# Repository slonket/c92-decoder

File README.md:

# c92-decoder

### An MM1/MM2/Lenz decoder for classic Märklin locomotives and the pre-mfx digital systems.

The c92 decoder was spawned out of a passion for the classic (pre-mfx) Märklin digital systems. The controllers of this era operated with three different protocols:
- MM1 (6020, 6021, 6022, 6023)
- MM2 (6021)
- Lenz (6027, 6029)

However, no single decoder from this era can operate on all three protocols, nor with all of their capabilities. Furthermore, there is a matrix of incompatibility between different controllers and combinations of decoders using MM1 and MM2. The c92 decoder is a superset of all decoder capabilities and their respective protocols; a universal classic decoder.

### Cloning

This project uses [`slonket-footprints`](https://github.com/slonket/slonket-footprints) as a submodule for all PCB designs. All KiCAD projects within this repository are configured to use the submodule libraries with local paths. Run the following to clone the repository with its submodule:
```
git clone --recurse-submodules https://github.com/slonket/c92-decoder.git
```

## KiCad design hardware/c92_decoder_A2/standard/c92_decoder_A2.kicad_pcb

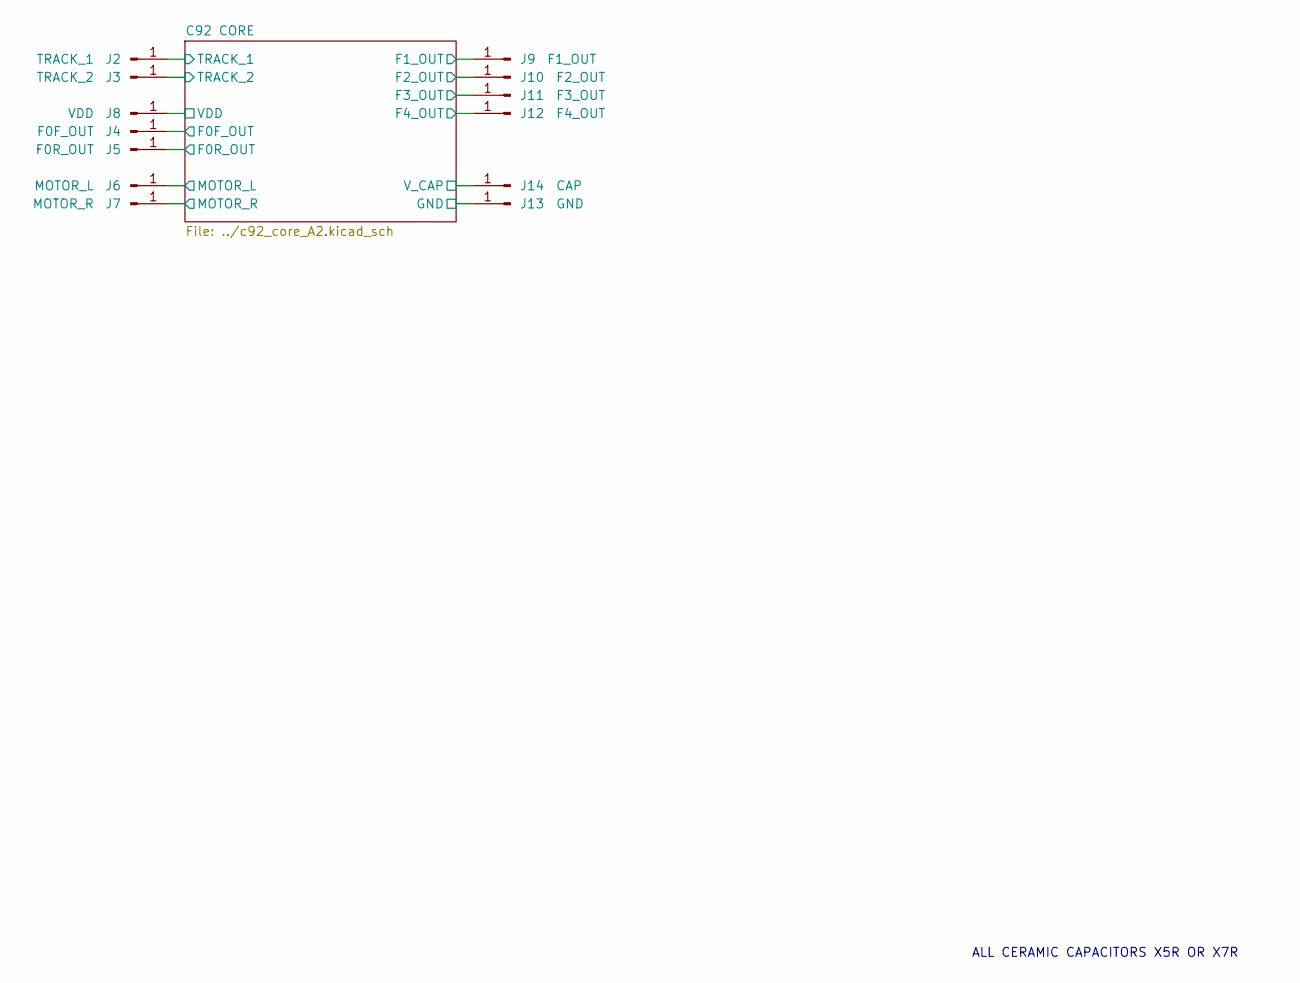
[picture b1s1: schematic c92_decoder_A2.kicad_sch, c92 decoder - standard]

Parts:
J2: TRACK_1; J_Pad_1mm_2mm
J3: TRACK_2; J_Pad_1mm_2mm
J4: F0F_OUT; J_Pad_1mm_2mm
J5: F0R_OUT; J_Pad_1mm_2mm
J6: MOTOR_L; J_Pad_1mm_2mm
J7: MOTOR_R; J_Pad_1mm_2mm
J8: VDD; J_Pad_1mm_2mm
J9: F1_OUT; J_Pad_1mm_2mm
J10: F2_OUT; J_Pad_1mm_2mm
J11: F3_OUT; J_Pad_1mm_2mm
J12: F4_OUT; J_Pad_1mm_2mm
J13: GND; J_Pad_1mm_2mm
J14: CAP; J_Pad_1mm_2mm

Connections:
/C92 CORE/F0F_OUT: J4.1 (Pin_1_1); also elsewhere on the board
/C92 CORE/F0R_OUT: J5.1 (Pin_1_1); also elsewhere on the board
/C92 CORE/F1_OUT: J9.1 (Pin_1_1); also elsewhere on the board
/C92 CORE/F2_OUT: J10.1 (Pin_1_1); also elsewhere on the board
/C92 CORE/F3_OUT: J11.1 (Pin_1_1); also elsewhere on the board
/C92 CORE/F4_OUT: J12.1 (Pin_1_1); also elsewhere on the board
/C92 CORE/MOTOR_L: J6.1 (Pin_1_1); also elsewhere on the board
/C92 CORE/MOTOR_R: J7.1 (Pin_1_1); also elsewhere on the board
/C92 CORE/TRACK_1: J2.1 (Pin_1_1); also elsewhere on the board
/C92 CORE/TRACK_2: J3.1 (Pin_1_1); also elsewhere on the board
/C92 CORE/V_CAP: J14.1 (Pin_1_1); also elsewhere on the board
GND: J13.1 (Pin_1_1); also elsewhere on the board
VDD: J8.1 (Pin_1_1); also elsewhere on the board

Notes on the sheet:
ALL CERAMIC CAPACITORS X5R OR X7R

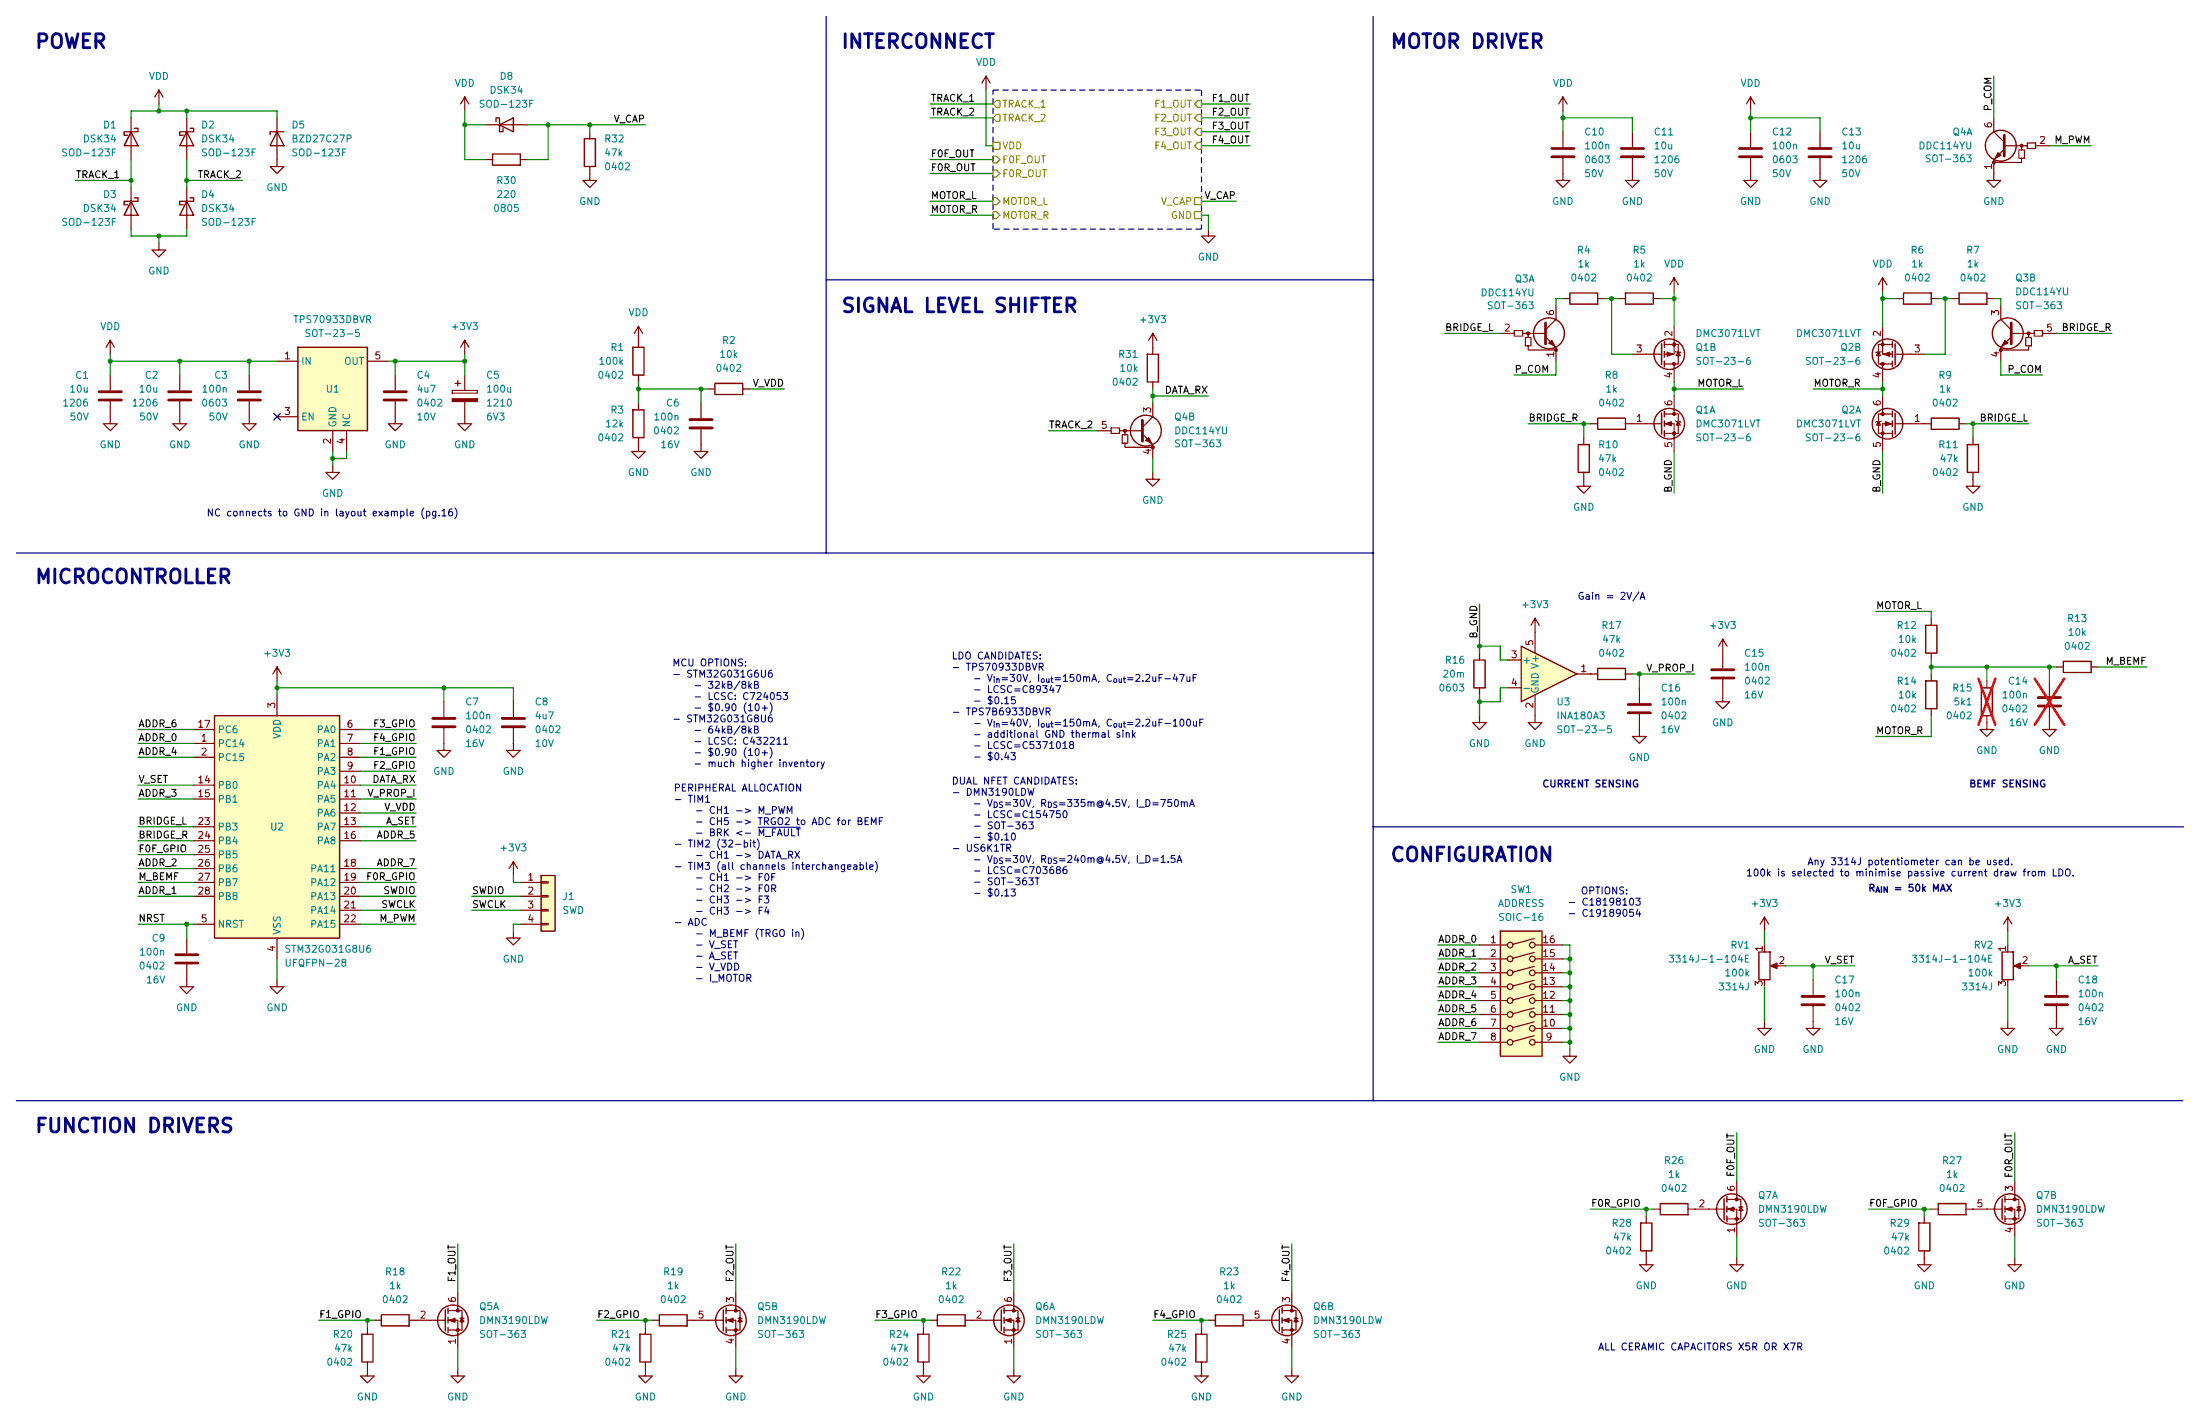
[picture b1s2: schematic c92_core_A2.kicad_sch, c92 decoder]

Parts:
C1, C2, C11, C13: 10u; C_1206; Voltage 50V; LCSC C13585
C3, C10, C12: 100n; C_0603; Voltage 50V; LCSC C14663
C4, C8: 4u7; C_0402; Voltage 10V; LCSC C23733
C5: 100u; CP_1210_CASE_B; Voltage 6V3; LCSC C16133
C6, C7, C9, C15, C16, C17, C18: 100n; C_0402; Voltage 16V; LCSC C1525
C14: 100n; C_0402; Voltage 16V; LCSC C1525; not fitted
D1, D2, D3, D4, D8: DSK34; D_SOD-123F; LCSC C7502709
D5: BZD27C27P; D_SOD-123F; LCSC C5455754
J1: SWD; J_Pad_4_1.5mm
Q1, Q2: DMC3071LVT; U_SOT-23-6; LCSC C17543297
Q3, Q4: DDC114YU; U_SOT-363; LCSC C151389
Q5, Q6, Q7: DMN3190LDW; U_SOT-363; LCSC C154750
R1: 100k; R_0402; LCSC C25741
R2, R12, R13, R14, R31: 10k; R_0402; LCSC C25744
R3: 12k; R_0402; LCSC C25752
R4, R5, R6, R7, R8, R9, R18, R19, R22, R23, R26, R27: 1k; R_0402; LCSC C11702
R10, R11, R17, R20, R21, R24, R25, R28, R29, R32: 47k; R_0402; LCSC C25792
R15: 5k1; R_0402; LCSC C25905; not fitted
R16: 20m; R_0603; LCSC C156372
R30: 220; R_0805; LCSC C17557
RV1, RV2: 3314J-1-104E; RV_BOURNS_3314J; LCSC C51284
SW1: ADDRESS; SW_DIP_8_P1.27; LCSC C18198103
U1: TPS70933DBVR; U_SOT-23-5; LCSC C89347
U2: STM32G031G8U6; U_STM_UFQFPN-28_4x4_P0.5; LCSC C432211
U3: INA180A3; U_SOT-23-5; LCSC C122882

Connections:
+3V3: C4.1, C5.1, C7.1, C8.1, C15.1, J1.1, R31.2, RV1.1, RV2.1, U1.5 (OUT), U2.3 (VDD), U3.5 (V+)
/C92 CORE/ADDR_0: SW1.1, U2.1 (PC14)
/C92 CORE/ADDR_1: SW1.2, U2.28 (PB8)
/C92 CORE/ADDR_2: SW1.3, U2.26 (PB6)
/C92 CORE/ADDR_3: SW1.4, U2.15 (PB1)
/C92 CORE/ADDR_4: SW1.5, U2.2 (PC15)
/C92 CORE/ADDR_5: SW1.6, U2.16 (PA8)
/C92 CORE/ADDR_6: SW1.7, U2.17 (PC6)
/C92 CORE/ADDR_7: SW1.8, U2.18 (PA11)
/C92 CORE/A_SET: C18.1, RV2.2, U2.13 (PA7)
/C92 CORE/BRIDGE_L: Q3.2 (B1), R9.1, R11.2, U2.23 (PB3)
/C92 CORE/BRIDGE_R: Q3.5 (B2), R8.1, R10.2, U2.24 (PB4)
/C92 CORE/B_GND: Q1.5 (S), Q2.5 (S), R16.1, U3.3 (+)
/C92 CORE/DATA_RX: Q4.3 (C2), R31.1, U2.10 (PA4)
/C92 CORE/F0F_GPIO: R27.1, R29.2, U2.25 (PB5)
/C92 CORE/F0F_OUT: Q7.6 (D); also elsewhere on the board
/C92 CORE/F0R_GPIO: R26.1, R28.2, U2.19 (PA12)
/C92 CORE/F0R_OUT: Q7.3 (D); also elsewhere on the board
/C92 CORE/F1_GPIO: R18.1, R20.2, U2.8 (PA2)
/C92 CORE/F1_OUT: Q5.6 (D); also elsewhere on the board
/C92 CORE/F2_GPIO: R19.1, R21.2, U2.9 (PA3)
/C92 CORE/F2_OUT: Q5.3 (D); also elsewhere on the board
/C92 CORE/F3_GPIO: R22.1, R24.2, U2.6 (PA0)
/C92 CORE/F3_OUT: Q6.6 (D); also elsewhere on the board
/C92 CORE/F4_GPIO: R23.1, R25.2, U2.7 (PA1)
/C92 CORE/F4_OUT: Q6.3 (D); also elsewhere on the board
/C92 CORE/MOTOR_L: Q1.4 (D), Q1.6 (D), R12.2; also elsewhere on the board
/C92 CORE/MOTOR_R: Q2.4 (D), Q2.6 (D), R14.1; also elsewhere on the board
/C92 CORE/M_BEMF: R13.2, U2.27 (PB7)
/C92 CORE/M_PWM: Q4.2 (B1), U2.22 (PA15)
/C92 CORE/NRST: C9.1, U2.5 (NRST)
/C92 CORE/P_COM: Q3.1 (E1), Q3.4 (E2), Q4.6 (C1)
/C92 CORE/SWCLK: J1.3, U2.21 (PA14)
/C92 CORE/SWDIO: J1.2, U2.20 (PA13)
/C92 CORE/TRACK_1: D1.2 (A), D3.1 (K); also elsewhere on the board
/C92 CORE/TRACK_2: D2.2 (A), D4.1 (K), Q4.5 (B2); also elsewhere on the board
/C92 CORE/V_CAP: D8.2 (A), R30.2, R32.2; also elsewhere on the board
/C92 CORE/V_PROP_I: C16.1, R17.2, U2.11 (PA5)
/C92 CORE/V_SET: C17.1, RV1.2, U2.14 (PB0)
/C92 CORE/V_VDD: R2.2, U2.12 (PA6)
GND: C1.2, C2.2, C3.2, C4.2, C5.2, C6.2, C7.2, C8.2, C9.2, C10.2, C11.2, C12.2, C13.2, C14.2, C15.2, C16.2, C17.2, C18.2, D3.2 (A), D4.2 (A), D5.2 (A), J1.4, Q4.1 (E1), Q4.4 (E2), Q5.1 (S), Q5.4 (S), Q6.1 (S), Q6.4 (S), Q7.1 (S), Q7.4 (S), R3.1, R10.1, R11.1, R15.1, R16.2, R20.1, R21.1, R24.1, R25.1, R28.1, R29.1, R32.1, RV1.3, RV2.3, SW1.9, SW1.10, SW1.11, SW1.12, SW1.13, SW1.14, SW1.15, SW1.16, U1.2 (GND), U1.4 (NC), U2.4 (VSS), U3.2 (GND), U3.4 (-); also elsewhere on the board
unnamed: C6.1, R1.1, R2.1, R3.2
unnamed: C14.1, R12.1, R13.1, R14.2, R15.2
unnamed: Q1.1 (G), R8.2
unnamed: Q1.3 (G), R4.2, R5.2
unnamed: Q2.1 (G), R9.2
unnamed: Q2.3 (G), R6.2, R7.1
unnamed: Q3.6 (C1), R4.1
unnamed: Q3.3 (C2), R7.2
unnamed: Q5.2 (G), R18.2
unnamed: Q5.5 (G), R19.2
unnamed: Q6.2 (G), R22.2
unnamed: Q6.5 (G), R23.2
unnamed: Q7.2 (G), R26.2
unnamed: Q7.5 (G), R27.2
unnamed: R17.1, U3.1
VDD: C1.1, C2.1, C3.1, C10.1, C11.1, C12.1, C13.1, D1.1 (K), D2.1 (K), D5.1 (K), D8.1 (K), Q1.2 (S), Q2.2 (S), R1.2, R5.1, R6.1, R30.1, U1.1 (IN); also elsewhere on the board

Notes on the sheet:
PERIPHERAL ALLOCATION - TIM1 - CH1 -> M_PWM - CH5 -> TRGO2 to ADC for BEMF - BRK <- ~{M_FAULT} - TIM2 (32-bit) - CH1 -> DATA_RX - TIM3 (all channels interchangeable) - CH1 -> F0F - CH2 -> F0R - CH3 -> F3 - CH3 -> F4 - ADC - M_BEMF (TRGO in) - V_SET - A_SET - V_VDD - I_MOTOR
Any 3314J potentiometer can be used. 100k is selected to minimise passive current draw from LDO.
MOTOR DRIVER
ALL CERAMIC CAPACITORS X5R OR X7R
SIGNAL LEVEL SHIFTER
POWER
Gain = 2V/A
DUAL NFET CANDIDATES: - DMN3190LDW - V_{DS}=30V, R_{DS}=335m@4.5V, I_D=750mA - LCSC=C154750 - SOT-363 - $0.10 - US6K1TR - V_{DS}=30V, R_{DS}=240m@4.5V, I_D=1.5A - LCSC=C703686 - SOT-363T - $0.13
OPTIONS: - C18198103 - C19189054
CURRENT SENSING
NC connects to GND in layout example (pg.16)
BEMF SENSING
MCU OPTIONS: - STM32G031G6U6 - 32kB/8kB - LCSC: C724053 - $0.90 (10+) - STM32G031G8U6 - 64kB/8kB - LCSC: C432211 - $0.90 (10+) - much higher inventory
INTERCONNECT
CONFIGURATION
FUNCTION DRIVERS
MICROCONTROLLER
LDO CANDIDATES: - TPS70933DBVR - V_{in}=30V, I_{out}=150mA, C_{out}=2.2uF-47uF - LCSC=C89347 - $0.15 - TPS7B6933DBVR - V_{in}=40V, I_{out}=150mA, C_{out}=2.2uF-100uF - additional GND thermal sink - LCSC=C5371018 - $0.43
R_{AIN} = 50k MAX

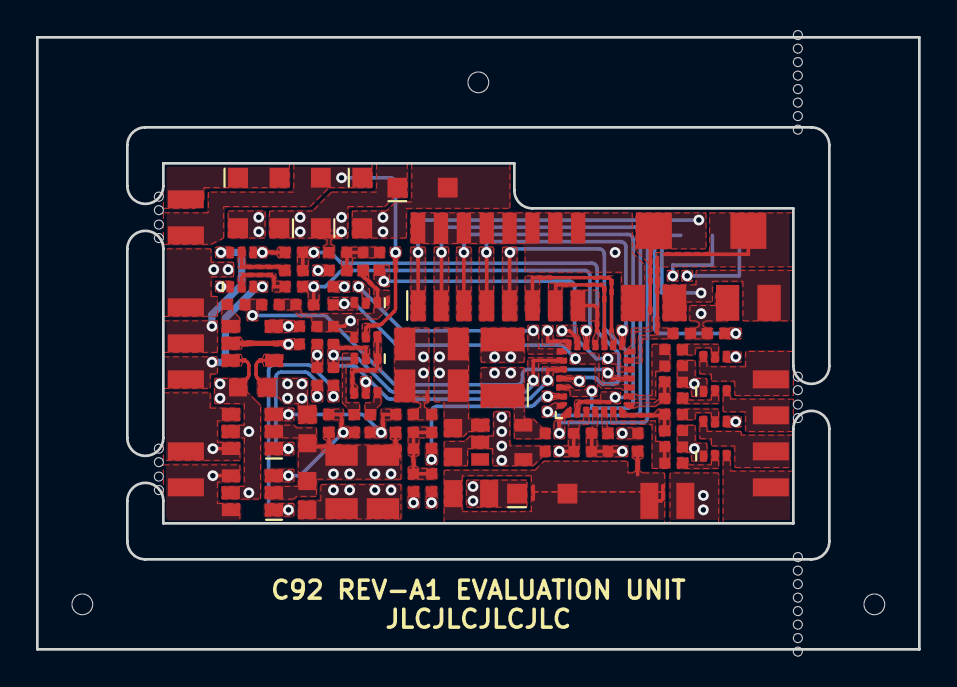
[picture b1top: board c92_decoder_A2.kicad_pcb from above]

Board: 4 copper layers, 49.0 x 34.0 mm, 83 parts (1 on the bottom side), 57 nets.

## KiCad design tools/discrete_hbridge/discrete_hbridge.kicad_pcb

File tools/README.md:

# c92-decoder - tools

### discrete_hbridge

A development board for the discrete H-bridge design used in the c92 decoder. The H-bridge is unique in being able to operate with low-side FETs always on, while PWM is applied only to the top FETs. This mode is necessary for BEMF measurement referenced to decoder ground.

### hubert_mounts

Mounting hardware for a breadboard to be fastened atop Hubert.

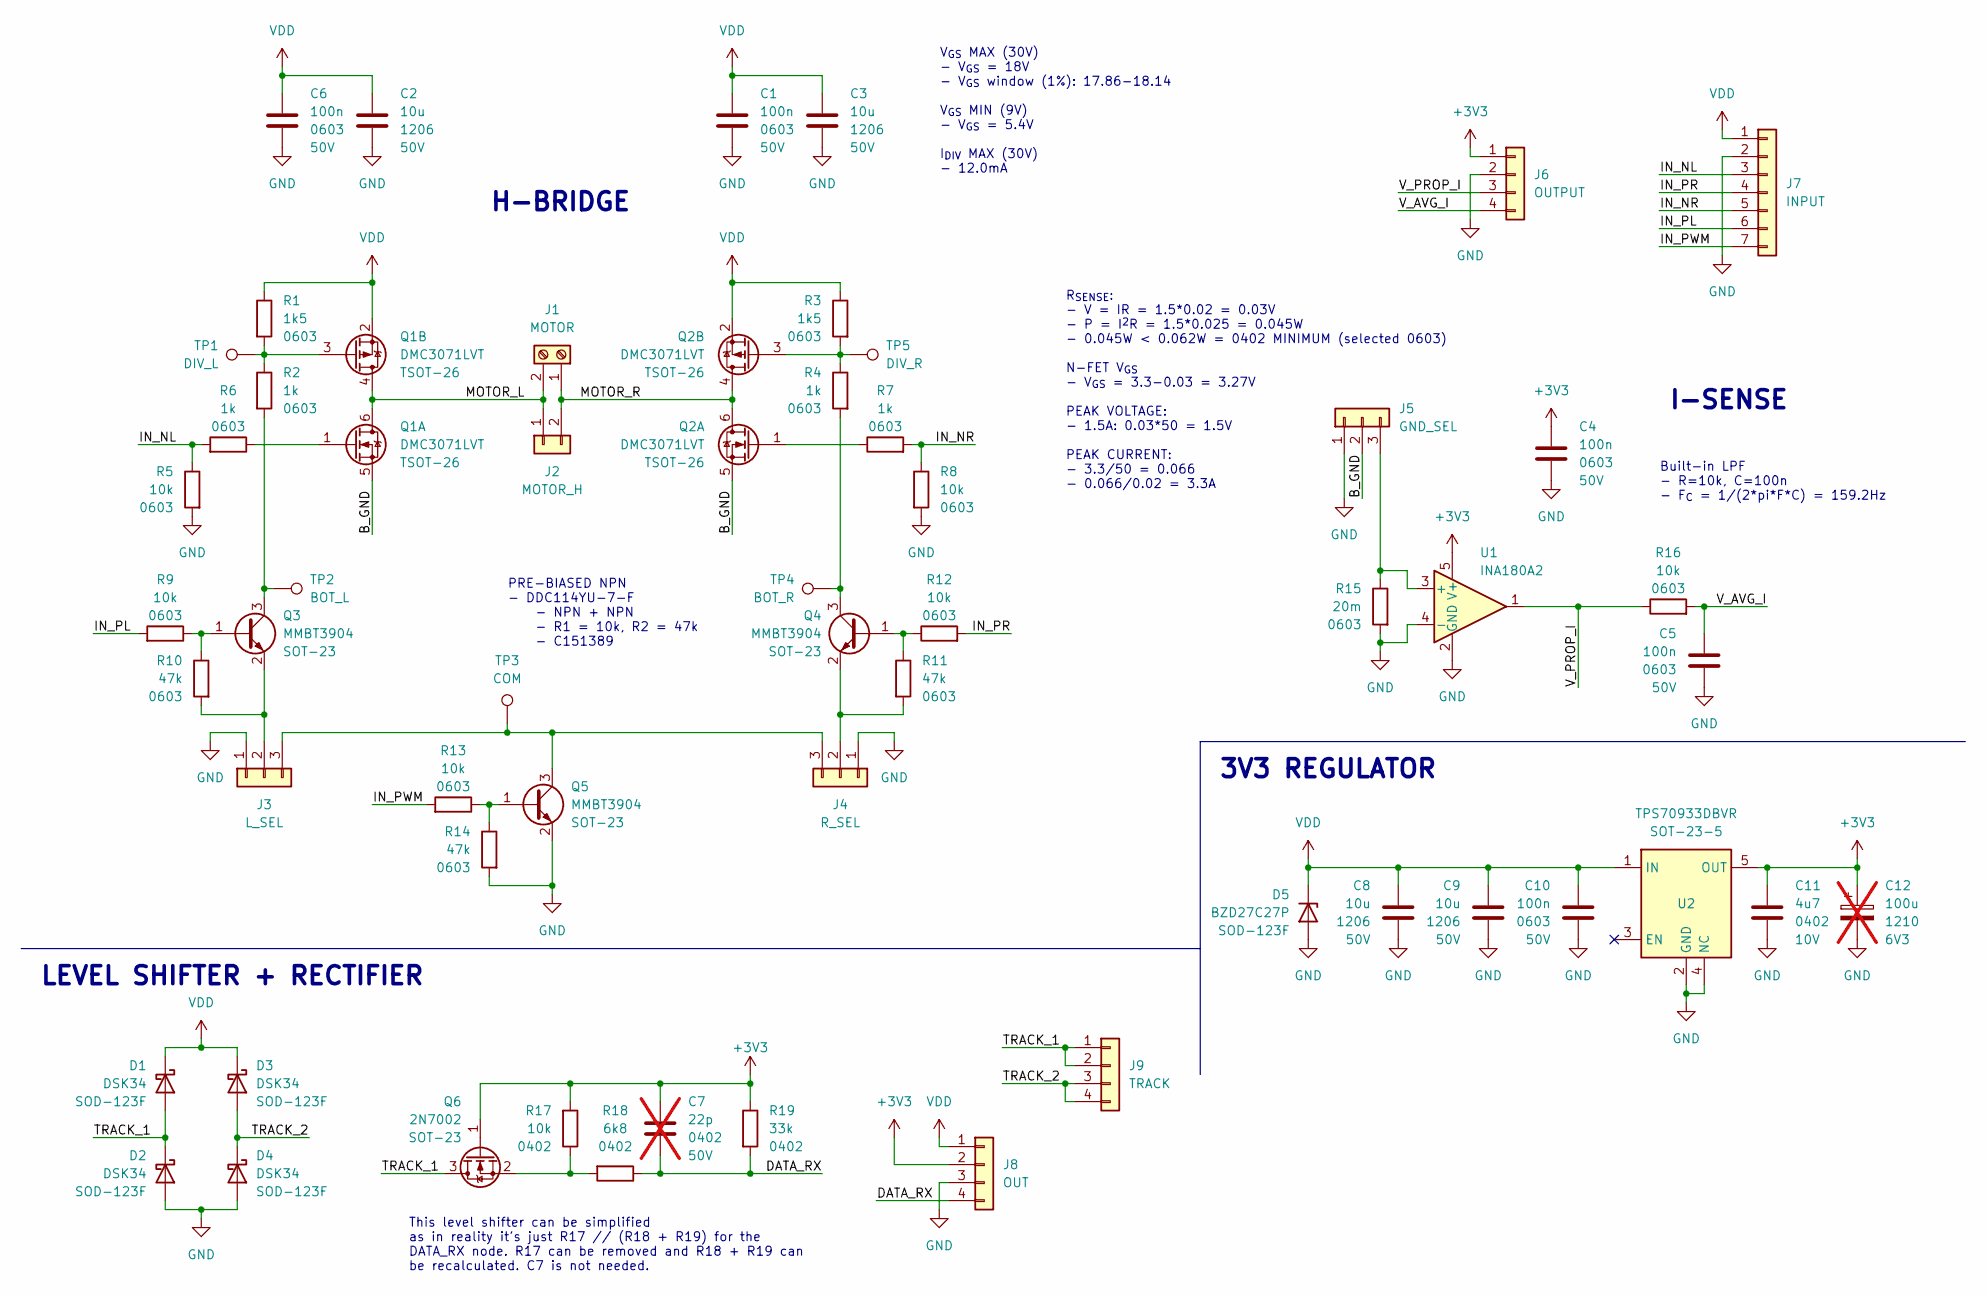
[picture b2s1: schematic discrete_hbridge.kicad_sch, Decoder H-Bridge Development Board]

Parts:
C1, C4, C5, C6: 100n; C_0603_1608Metric; Voltage 50V; LCSC C14663
C2, C3: 10u; C_1206_3216Metric; Voltage 50V; LCSC C13585
C7: 22p; C_0402; Voltage 50V; LCSC C1653; not fitted
C8, C9: 10u; C_1206; Voltage 50V; LCSC C13585
C10: 100n; C_0603; Voltage 50V; LCSC C14663
C11: 4u7; C_0402; Voltage 10V; LCSC C23733
C12: 100u; CP_1210_CASE_B; Voltage 6V3; LCSC C16133; not fitted
D1, D2, D3, D4: DSK34; D_SOD-123F; LCSC C7502709
D5: BZD27C27P; D_SOD-123F; LCSC C5455754
J1: MOTOR; TerminalBlock_MaiXu_MX126-5.0-02P_1x02_P5.00mm
J2: MOTOR_H; PinHeader_1x02_P2.54mm_Vertical
J3: L_SEL; PinHeader_1x03_P2.54mm_Vertical
J4: R_SEL; PinHeader_1x03_P2.54mm_Vertical
J5: GND_SEL; PinHeader_1x03_P2.54mm_Vertical
J6: OUTPUT; PinHeader_1x04_P2.54mm_Vertical
J7: INPUT; PinHeader_1x07_P2.54mm_Vertical
J8: OUT; PinHeader_1x04_P2.54mm_Vertical
J9: TRACK; PinHeader_1x04_P2.54mm_Vertical
Q1, Q2: DMC3071LVT; TSOT-23-6; LCSC C17543297
Q3, Q4, Q5: MMBT3904; SOT-23; LCSC C7420353
Q6: 2N7002; U_SOT-23; LCSC C8545
R1, R3: 1k5; R_0603_1608Metric; LCSC C22843
R2, R4, R6, R7: 1k; R_0603_1608Metric; LCSC C21190
R5, R8, R9, R12, R13, R16: 10k; R_0603_1608Metric; LCSC C25804
R10, R11, R14: 47k; R_0603_1608Metric; LCSC C25819
R15: 20m; R_0603_1608Metric; LCSC C156372
R17: 10k; R_0402; LCSC C25744
R18: 6k8; R_0402; LCSC C25917
R19: 33k; R_0402; LCSC C25779
TP1: DIV_L; TP_Loop
TP2: BOT_L; TP_Loop
TP3: COM; TP_Loop
TP4: BOT_R; TP_Loop
TP5: DIV_R; TP_Loop
U1: INA180A2; SOT-23-5; LCSC C192764
U2: TPS70933DBVR; U_SOT-23-5; LCSC C89347

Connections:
+3V3: C4.1, C7.1, C11.1, C12.1, J6.1, J8.2, Q6.1 (G), R17.2, R19.1, U1.5 (V+), U2.5 (OUT)
/B_GND: J5.2, Q1.5 (S), Q2.5 (S)
/DATA_RX: C7.2, J8.4, R18.1, R19.2
/IN_NL: J7.3, R5.1, R6.2
/IN_NR: J7.5, R7.2, R8.1
/IN_PL: J7.6, R9.2
/IN_PR: J7.4, R12.2
/IN_PWM: J7.7, R13.2
/MOTOR_L: J1.2, J2.1, Q1.4 (D), Q1.6 (D)
/MOTOR_R: J1.1, J2.2, Q2.4 (D), Q2.6 (D)
/TRACK_1: D1.2 (A), D2.1 (K), J9.1, J9.2, Q6.3 (D)
/TRACK_2: D3.2 (A), D4.1 (K), J9.3, J9.4
/V_AVG_I: C5.1, J6.4, R16.2
/V_PROP_I: J6.3, R16.1, U1.1
GND: C1.2, C2.2, C3.2, C4.2, C5.2, C6.2, C8.2, C9.2, C10.2, C11.2, C12.2, D2.2 (A), D4.2 (A), D5.2 (A), J3.1, J4.1, J5.1, J6.2, J7.2, J8.3, Q5.2 (E), R5.2, R8.2, R14.2, R15.2, U1.2 (GND), U1.4 (-), U2.2 (GND), U2.4 (NC)
unnamed: J3.2, Q3.2 (E), R10.2
unnamed: J3.3, J4.3, Q5.3 (C), TP3.1 (1_1)
unnamed: J4.2, Q4.2 (E), R11.2
unnamed: J5.3, R15.1, U1.3 (+)
unnamed: Q1.1 (G), R6.1
unnamed: Q1.3 (G), R1.2, R2.1, TP1.1 (1_1)
unnamed: Q2.1 (G), R7.1
unnamed: Q2.3 (G), R3.2, R4.1, TP5.1 (1_1)
unnamed: Q3.1 (B), R9.1, R10.1
unnamed: Q3.3 (C), R2.2, TP2.1 (1_1)
unnamed: Q4.1 (B), R11.1, R12.1
unnamed: Q4.3 (C), R4.2, TP4.1 (1_1)
unnamed: Q5.1 (B), R13.1, R14.1
unnamed: Q6.2 (S), R17.1, R18.2
VDD: C1.1, C2.1, C3.1, C6.1, C8.1, C9.1, C10.1, D1.1 (K), D3.1 (K), D5.1 (K), J7.1, J8.1, Q1.2 (S), Q2.2 (S), R1.1, R3.1, U2.1 (IN)

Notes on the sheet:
H-BRIDGE
I-SENSE
3V3 REGULATOR
V_{GS} MAX (30V) - V_{GS} = 18V - V_{GS} window (1%): 17.86-18.14 V_{GS} MIN (9V) - V_{GS} = 5.4V I_{DIV} MAX (30V) - 12.0mA
PRE-BIASED NPN - DDC114YU-7-F - NPN + NPN - R1 = 10k, R2 = 47k - C151389
This level shifter can be simplified as in reality it's just R17 // (R18 + R19) for the DATA_RX node. R17 can be removed and R18 + R19 can be recalculated. C7 is not needed.
Built-in LPF - R=10k, C=100n - F_{C} = 1/(2*pi*F*C) = 159.2Hz
LEVEL SHIFTER + RECTIFIER
R_{SENSE}: - V = IR = 1.5*0.02 = 0.03V - P = I^{2}R = 1.5*0.025 = 0.045W - 0.045W < 0.062W = 0402 MINIMUM (selected 0603) N-FET V_{GS} - V_{GS} = 3.3-0.03 = 3.27V PEAK VOLTAGE: - 1.5A: 0.03*50 = 1.5V PEAK CURRENT: - 3.3/50 = 0.066 - 0.066/0.02 = 3.3A

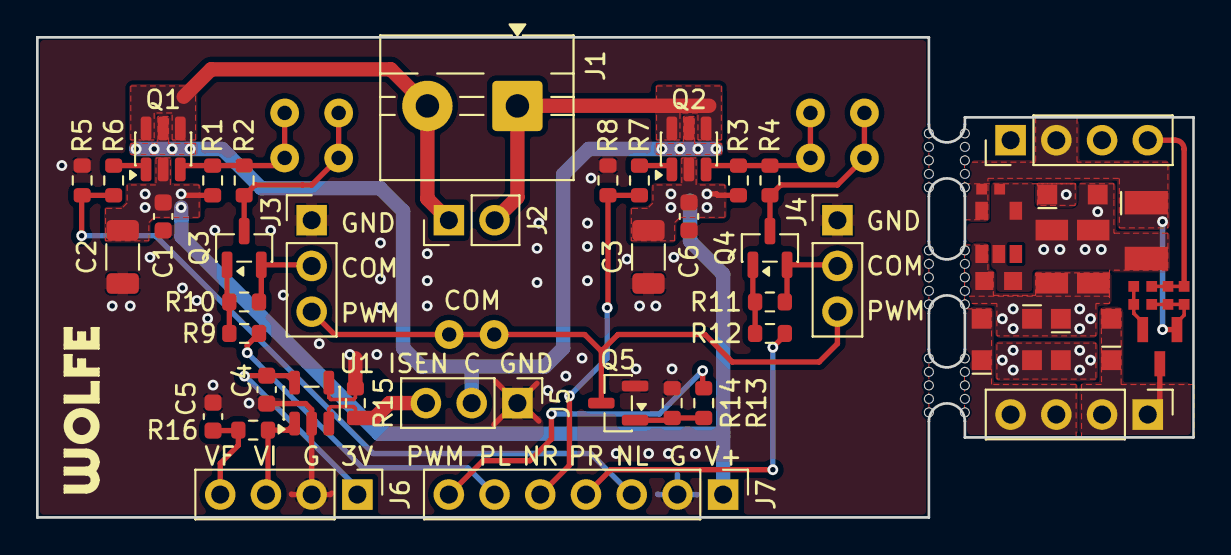
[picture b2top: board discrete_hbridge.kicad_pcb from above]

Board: 2 copper layers, 64.2 x 26.7 mm, 58 parts (0 on the bottom side), 30 nets.

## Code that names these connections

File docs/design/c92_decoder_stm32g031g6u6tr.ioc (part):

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Mcu.Name=STM32G031G(4-6-8)Ux
Mcu.Package=UFQFPN28
Mcu.UserName=STM32G031G6Ux
PA0.GPIOParameters=GPIO_Label
PA0.GPIO_Label=F4
PA0.Signal=GPIO_Output
PA1.GPIOParameters=GPIO_Label
PA1.GPIO_Label=F3
PA1.Signal=GPIO_Output
PA11\ [PA9].GPIOParameters=GPIO_Label
PA11\ [PA9].GPIO_Label=ADDR_7
PA11\ [PA9].Signal=GPIO_Input
PA12\ [PA10].GPIOParameters=GPIO_Label
PA12\ [PA10].GPIO_Label=F0R
PA12\ [PA10].Signal=GPIO_Output
PA13.Mode=Serial_Wire
PA13.Signal=SYS_SWDIO
PA14-BOOT0.Mode=Serial_Wire
PA14-BOOT0.Signal=SYS_SWCLK
PA15.GPIOParameters=GPIO_Label
PA15.GPIO_Label=M_PWM
PA15.Signal=S_TIM2_CH1_ETR
PA2.GPIOParameters=GPIO_Label
PA2.GPIO_Label=F2
PA2.Signal=GPIO_Output
PA3.GPIOParameters=GPIO_Label
PA3.GPIO_Label=F1
PA3.Signal=GPIO_Output
PA4.GPIOParameters=GPIO_Label
PA4.GPIO_Label=DATA_IN
PA4.Signal=S_TIM14_CH1
PA5.GPIOParameters=GPIO_Label
PA5.GPIO_Label=V_PROP_I
PA5.Mode=IN5
PA5.Signal=ADC1_IN5
PA6.GPIOParameters=GPIO_Label
PA6.GPIO_Label=V_VDD
PA6.Mode=IN6
PA6.Signal=ADC1_IN6
PA7.GPIOParameters=GPIO_Label
PA7.GPIO_Label=A_SET
PA7.Mode=IN7
PA7.Signal=ADC1_IN7
PA8.GPIOParameters=GPIO_Label
PA8.GPIO_Label=ADDR_5
PA8.Signal=GPIO_Input
PB0.GPIOParameters=GPIO_Label
PB0.GPIO_Label=V_SET
PB0.Mode=IN8
PB0.Signal=ADC1_IN8
PB1.GPIOParameters=GPIO_Label
PB1.GPIO_Label=F0F
PB1.Signal=GPIO_Output
PB3.GPIOParameters=GPIO_Label
PB3.GPIO_Label=BRIDGE_L
PB3.Signal=GPIO_Output
PB4.GPIOParameters=GPIO_Label
PB4.GPIO_Label=BRIDGE_R
PB4.Signal=GPIO_Output
PB5.GPIOParameters=GPIO_Label
PB5.GPIO_Label=ADDR_4
PB5.Signal=GPIO_Input
PB6.GPIOParameters=GPIO_Label
PB6.GPIO_Label=ADDR_2
PB6.Signal=GPIO_Input
PB7.GPIOParameters=GPIO_Label
PB7.GPIO_Label=M_BEMF
PB7.Mode=IN11
PB7.Signal=ADC1_IN11
PB8.GPIOParameters=GPIO_Label
PB8.GPIO_Label=ADDR_1
PB8.Signal=GPIO_Input
PC14-OSC32_IN\ (PC14).GPIOParameters=GPIO_Label
PC14-OSC32_IN\ (PC14).GPIO_Label=ADDR_0
PC14-OSC32_IN\ (PC14).Signal=GPIO_Input
PC15-OSC32_OUT\ (PC15).GPIOParameters=GPIO_Label
PC15-OSC32_OUT\ (PC15).GPIO_Label=ADDR_3
PC15-OSC32_OUT\ (PC15).Signal=GPIO_Input
PC6.GPIOParameters=GPIO_Label
PC6.GPIO_Label=ADDR_6
PC6.Signal=GPIO_Input
RCC.HSE_VALUE=8000000
RCC.SYSCLKFreq_VALUE=64000000
RCC.SYSCLKSource=RCC_SYSCLKSOURCE_PLLCLK
board=custom
